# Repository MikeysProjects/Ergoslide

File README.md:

# Ergoslide

## Repo layout

- .github
  - Workflows that build the firmware(s) for the microcontroller that runs the keyboard
- 3d files
  - The source Fusion 360 projects that produce the models for the case
- boards
  - The ZMK shield configuration
- config
  - Global ZMK shield configuration
- images
  - Images (e.g. PNGs, DXFs) needed to create the board or case
- models
  - Output models from Fusion 360 for the case
- pcb
  - The Kicad project for the keyboard PCB
- plates
  - Layouts exported from KLE, useful for creating either 3d models or DXFs for having the top plate manufactured, or automating the layout of the PCB
- zephyr
  - Root Zephyr config

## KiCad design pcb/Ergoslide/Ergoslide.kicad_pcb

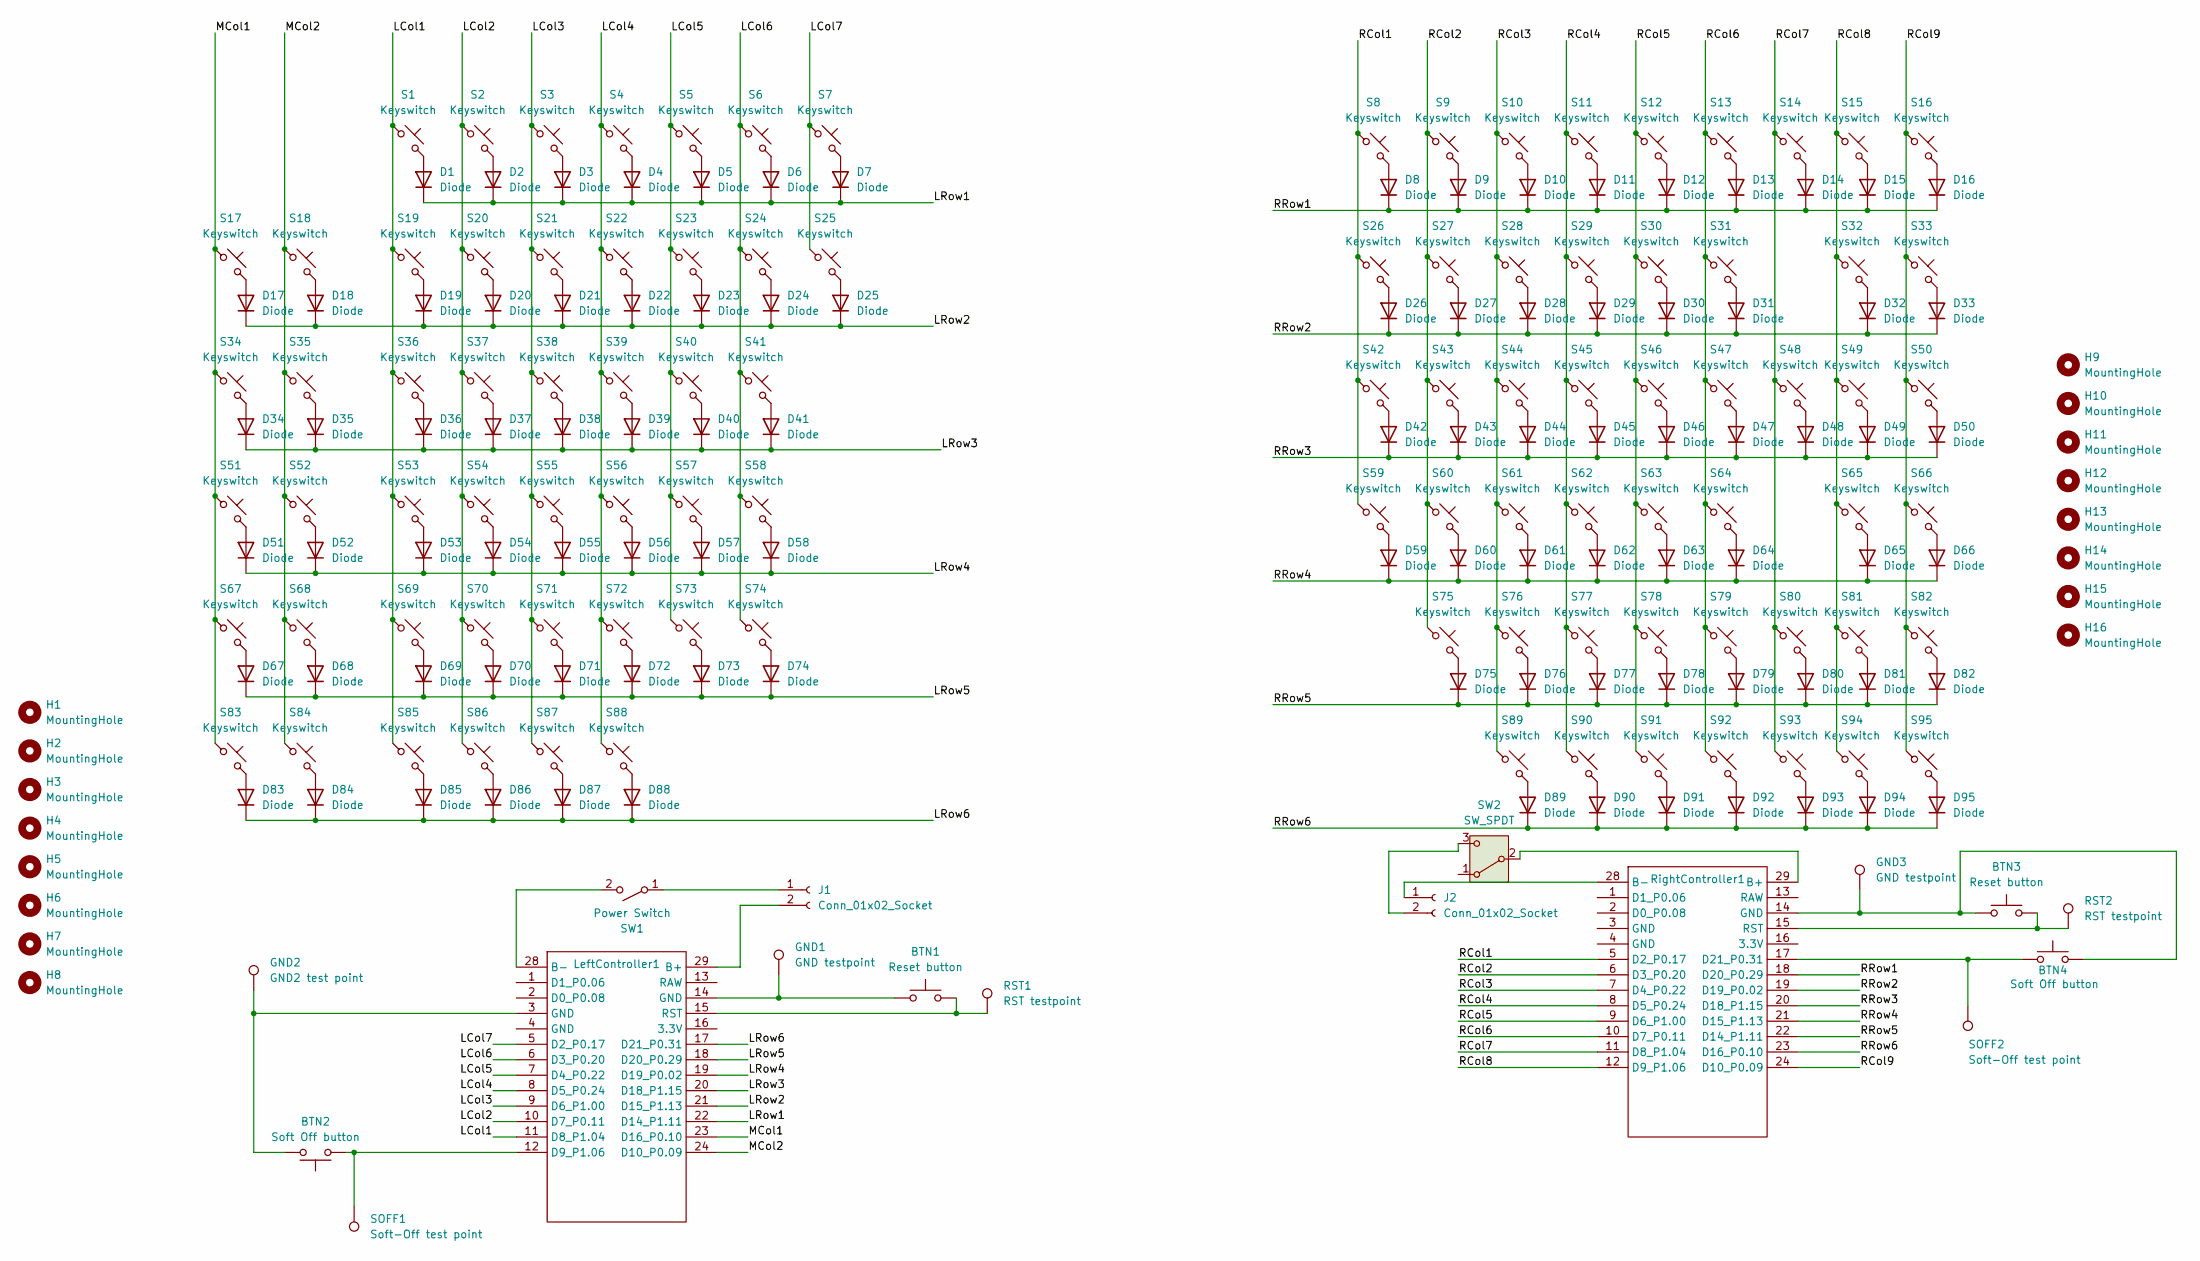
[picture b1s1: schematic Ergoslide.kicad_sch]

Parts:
BTN1, BTN3: Reset button; SW_TL3330AF260QG
BTN2, BTN4: Soft Off button; SW_TL3330AF260QG
D1, D2, D3, D4, D5, D6, D7, D8, D9, D10, D11, D12, D13, D14, D15, D16, D17, D18, D19, D20, D21, D22, D23, D24, D25, D26, D27, D28, D29, D30, D31, D32, D33, D34, D35, D36, D37, D38, D39, D40, D41, D42, D43, D44, D45, D46, D47, D48, D49, D50, D51, D52, D53, D54, D55, D56, D57, D58, D59, D60, D61, D62, D63, D64, D65, D66, D67, D68, D69, D70, D71, D72, D73, D74, D75, D76, D77, D78, D79, D80, D81, D82, D83, D84, D85, D86, D87, D88, D89, D90, D91, D92, D93, D94, D95: Diode; Diode_SOD-123
GND1, GND3: GND testpoint; TestPoint_Pad_2.0x2.0mm
GND2: GND2 test point; TestPoint_Pad_2.0x2.0mm
H1, H2, H3, H4, H5, H6, H7, H8, H9, H10, H11, H12, H13, H14, H15, H16: MountingHole; MountingHole_2.2mm_M2
J1, J2: Conn_01x02_Socket; JST_PH_S2B-PH-K_1x02_P2.00mm_Horizontal
LeftController1: SuperMini NRF52840
RST1, RST2: RST testpoint; TestPoint_Pad_2.0x2.0mm
RightController1: SimpleMini NRF52840
S1, S2, S3, S4, S5, S6, S7, S8, S9, S10, S11, S12, S13, S14, S15, S16, S17, S18, S19, S20, S21, S22, S23, S24, S25, S26, S27, S28, S29, S30, S31, S33, S34, S35, S37, S38, S39, S40, S41, S42, S43, S44, S45, S46, S47, S48, S50, S51, S52, S54, S55, S56, S57, S58, S59, S60, S61, S62, S63, S64, S66, S67, S68, S70, S71, S72, S73, S74, S75, S76, S77, S78, S79, S81, S82, S83, S84, S91, S93, S94, S95: Keyswitch; Gateron-KS33-Hotswap-1U
S32: Keyswitch; Gateron-KS33-Hotswap-2U
S36, S49: Keyswitch; Gateron-KS33-Hotswap-1.5U
S53, S80: Keyswitch; Gateron-KS33-Hotswap-1.75U
S65, S69, S89: Keyswitch; Gateron-KS33-Hotswap-2.25U Stabilized
S85, S86, S87, S90, S92: Keyswitch; Gateron-KS33-Hotswap-1.25U
S88: Keyswitch; Gateron-KS33-Hotswap-2.75U Stabilized
SOFF1, SOFF2: Soft-Off test point; TestPoint_Pad_2.0x2.0mm
SW1: Power Switch; SW_SPDT_CK_JS102011SAQN
SW2: SW_SPDT; SW_SPDT_CK_JS102011SAQN

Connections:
/LCol1: LeftController1.11 (D8_P1.04), S1.1, S19.1, S36.1, S53.1, S69.1, S85.1
/LCol2: LeftController1.10 (D7_P0.11), S2.1, S20.1, S37.1, S54.1, S70.1, S86.1
/LCol3: LeftController1.9 (D6_P1.00), S3.1, S21.1, S38.1, S55.1, S71.1, S87.1
/LCol4: LeftController1.8 (D5_P0.24), S4.1, S22.1, S39.1, S56.1, S72.1, S88.1
/LCol5: LeftController1.7 (D4_P0.22), S5.1, S23.1, S40.1, S57.1, S73.1
/LCol6: LeftController1.6 (D3_P0.20), S6.1, S24.1, S41.1, S58.1, S74.1
/LCol7: LeftController1.5 (D2_P0.17), S7.1, S25.1
/LRow1: D1.1 (K), D2.1 (K), D3.1 (K), D4.1 (K), D5.1 (K), D6.1 (K), D7.1 (K), LeftController1.22 (D14_P1.11)
/LRow2: D17.1 (K), D18.1 (K), D19.1 (K), D20.1 (K), D21.1 (K), D22.1 (K), D23.1 (K), D24.1 (K), D25.1 (K), LeftController1.21 (D15_P1.13)
/LRow3: D34.1 (K), D35.1 (K), D36.1 (K), D37.1 (K), D38.1 (K), D39.1 (K), D40.1 (K), D41.1 (K), LeftController1.20 (D18_P1.15)
/LRow4: D51.1 (K), D52.1 (K), D53.1 (K), D54.1 (K), D55.1 (K), D56.1 (K), D57.1 (K), D58.1 (K), LeftController1.19 (D19_P0.02)
/LRow5: D67.1 (K), D68.1 (K), D69.1 (K), D70.1 (K), D71.1 (K), D72.1 (K), D73.1 (K), D74.1 (K), LeftController1.18 (D20_P0.29)
/LRow6: D83.1 (K), D84.1 (K), D85.1 (K), D86.1 (K), D87.1 (K), D88.1 (K), LeftController1.17 (D21_P0.31)
/MCol1: LeftController1.23 (D16_P0.10), S17.1, S34.1, S51.1, S67.1, S83.1
/MCol2: LeftController1.24 (D10_P0.09), S18.1, S35.1, S52.1, S68.1, S84.1
/RCol1: RightController1.5 (D2_P0.17), S8.1, S26.1, S42.1, S59.1
/RCol2: RightController1.6 (D3_P0.20), S9.1, S27.1, S43.1, S60.1, S75.1
/RCol3: RightController1.7 (D4_P0.22), S10.1, S28.1, S44.1, S61.1, S76.1, S89.1
/RCol4: RightController1.8 (D5_P0.24), S11.1, S29.1, S45.1, S62.1, S77.1, S90.1
/RCol5: RightController1.9 (D6_P1.00), S12.1, S30.1, S46.1, S63.1, S78.1, S91.1
/RCol6: RightController1.10 (D7_P0.11), S13.1, S31.1, S47.1, S64.1, S79.1, S92.1
/RCol7: RightController1.11 (D8_P1.04), S14.1, S48.1, S80.1, S93.1
/RCol8: RightController1.12 (D9_P1.06), S15.1, S32.1, S49.1, S65.1, S81.1, S94.1
/RCol9: RightController1.24 (D10_P0.09), S16.1, S33.1, S50.1, S66.1, S82.1, S95.1
/RRow1: D8.1 (K), D9.1 (K), D10.1 (K), D11.1 (K), D12.1 (K), D13.1 (K), D14.1 (K), D15.1 (K), D16.1 (K), RightController1.18 (D20_P0.29)
/RRow2: D26.1 (K), D27.1 (K), D28.1 (K), D29.1 (K), D30.1 (K), D31.1 (K), D32.1 (K), D33.1 (K), RightController1.19 (D19_P0.02)
/RRow3: D42.1 (K), D43.1 (K), D44.1 (K), D45.1 (K), D46.1 (K), D47.1 (K), D48.1 (K), D49.1 (K), D50.1 (K), RightController1.20 (D18_P1.15)
/RRow4: D59.1 (K), D60.1 (K), D61.1 (K), D62.1 (K), D63.1 (K), D64.1 (K), D65.1 (K), D66.1 (K), RightController1.21 (D15_P1.13)
/RRow5: D75.1 (K), D76.1 (K), D77.1 (K), D78.1 (K), D79.1 (K), D80.1 (K), D81.1 (K), D82.1 (K), RightController1.22 (D14_P1.11)
/RRow6: D89.1 (K), D90.1 (K), D91.1 (K), D92.1 (K), D93.1 (K), D94.1 (K), D95.1 (K), RightController1.23 (D16_P0.10)
unnamed: BTN2.2, GND2.1, LeftController1.3 (GND)
unnamed: BTN3.1, BTN4.2, GND3.1, RightController1.14 (GND)
unnamed: D1.2 (A), S1.2
unnamed: D2.2 (A), S2.2
unnamed: D3.2 (A), S3.2
unnamed: D4.2 (A), S4.2
unnamed: D5.2 (A), S5.2
unnamed: D6.2 (A), S6.2
unnamed: D7.2 (A), S7.2
unnamed: D8.2 (A), S8.2
unnamed: D9.2 (A), S9.2
unnamed: D10.2 (A), S10.2
unnamed: D11.2 (A), S11.2
unnamed: D12.2 (A), S12.2
unnamed: D13.2 (A), S13.2
unnamed: D14.2 (A), S14.2
unnamed: D15.2 (A), S15.2
unnamed: D16.2 (A), S16.2
unnamed: D17.2 (A), S17.2
unnamed: D18.2 (A), S18.2
unnamed: D19.2 (A), S19.2
unnamed: D20.2 (A), S20.2
unnamed: D21.2 (A), S21.2
unnamed: D22.2 (A), S22.2
unnamed: D23.2 (A), S23.2
unnamed: D24.2 (A), S24.2
unnamed: D25.2 (A), S25.2
unnamed: D26.2 (A), S26.2
unnamed: D27.2 (A), S27.2
unnamed: D28.2 (A), S28.2
unnamed: D29.2 (A), S29.2
unnamed: D30.2 (A), S30.2
unnamed: D31.2 (A), S31.2
unnamed: D32.2 (A), S32.2
unnamed: D33.2 (A), S33.2
unnamed: D34.2 (A), S34.2
unnamed: D35.2 (A), S35.2
unnamed: D36.2 (A), S36.2
unnamed: D37.2 (A), S37.2
unnamed: D38.2 (A), S38.2
unnamed: D39.2 (A), S39.2
unnamed: D40.2 (A), S40.2
unnamed: D41.2 (A), S41.2
unnamed: D42.2 (A), S42.2
unnamed: D43.2 (A), S43.2
unnamed: D44.2 (A), S44.2
unnamed: D45.2 (A), S45.2
unnamed: D46.2 (A), S46.2
unnamed: D47.2 (A), S47.2
unnamed: D48.2 (A), S48.2
unnamed: D49.2 (A), S49.2
unnamed: D50.2 (A), S50.2
unnamed: D51.2 (A), S51.2
unnamed: D52.2 (A), S52.2
unnamed: D53.2 (A), S53.2
unnamed: D54.2 (A), S54.2
unnamed: D55.2 (A), S55.2
unnamed: D56.2 (A), S56.2
unnamed: D57.2 (A), S57.2
unnamed: D58.2 (A), S58.2
unnamed: D59.2 (A), S59.2
unnamed: D60.2 (A), S60.2
unnamed: D61.2 (A), S61.2
unnamed: D62.2 (A), S62.2
unnamed: D63.2 (A), S63.2
unnamed: D64.2 (A), S64.2
unnamed: D65.2 (A), S65.2
unnamed: D66.2 (A), S66.2
unnamed: D67.2 (A), S67.2
unnamed: D68.2 (A), S68.2
unnamed: D69.2 (A), S69.2
unnamed: D70.2 (A), S70.2
unnamed: D71.2 (A), S71.2
unnamed: D72.2 (A), S72.2
unnamed: D73.2 (A), S73.2
unnamed: D74.2 (A), S74.2
unnamed: D75.2 (A), S75.2
unnamed: D76.2 (A), S76.2
unnamed: D77.2 (A), S77.2
unnamed: D78.2 (A), S78.2
unnamed: D79.2 (A), S79.2
unnamed: D80.2 (A), S80.2
unnamed: D81.2 (A), S81.2
unnamed: D82.2 (A), S82.2
unnamed: D83.2 (A), S83.2
unnamed: D84.2 (A), S84.2
unnamed: D85.2 (A), S85.2
unnamed: D86.2 (A), S86.2
unnamed: D87.2 (A), S87.2
unnamed: D88.2 (A), S88.2
unnamed: D89.2 (A), S89.2
unnamed: D90.2 (A), S90.2
unnamed: D91.2 (A), S91.2
unnamed: D92.2 (A), S92.2
unnamed: D93.2 (A), S93.2
unnamed: D94.2 (A), S94.2
unnamed: D95.2 (A), S95.2
unnamed 128: BTN1.1, GND1.1, LeftController1.14 (GND); also elsewhere on the board
unnamed: J1.1, SW1.1 (A)
unnamed: J1.2, LeftController1.29 (B+)
unnamed: J2.1, RightController1.28 (B-)
unnamed: J2.2, SW2.3 (C)
unnamed: LeftController1.28 (B-), SW1.2 (B)
unnamed 134: LeftController1.1 (D1_P0.06); also elsewhere on the board
unnamed: BTN2.1, LeftController1.12 (D9_P1.06), SOFF1.1
unnamed: BTN1.2, LeftController1.15 (RST), RST1.1
unnamed: RightController1.29 (B+), SW2.2 (B)
unnamed: BTN4.1, RightController1.17 (D21_P0.31), SOFF2.1
unnamed: BTN3.2, RST2.1, RightController1.15 (RST)

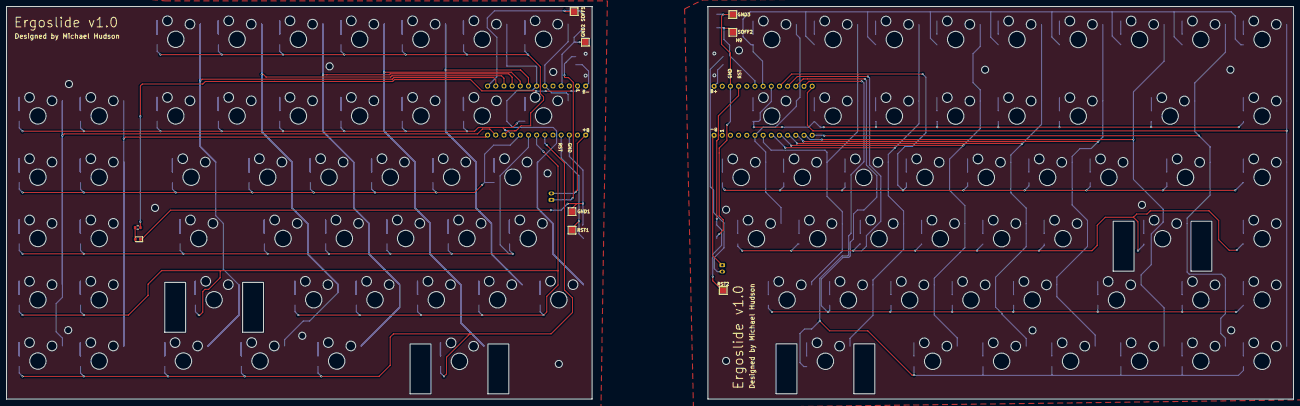
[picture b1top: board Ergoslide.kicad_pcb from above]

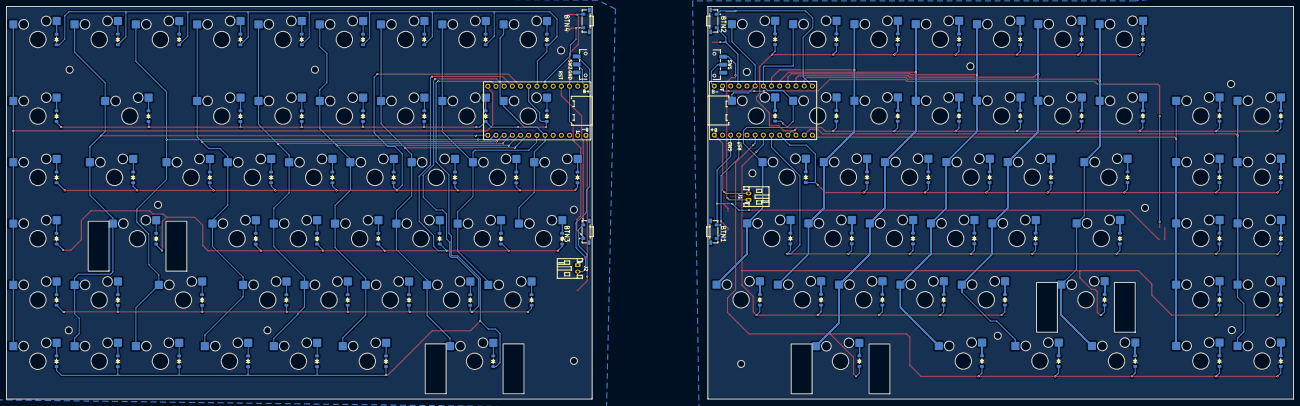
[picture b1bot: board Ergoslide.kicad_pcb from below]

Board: 2 copper layers, 400.0 x 122.0 mm, 225 parts (200 on the bottom side), 140 nets.

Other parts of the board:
D96: LED; LED_0603_1608Metric
R1: Resistor; R_0603_1608Metric

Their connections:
unnamed: D96.2 (A), R1.2
unnamed 128: D96.1 (K); also elsewhere on the board
unnamed 134: R1.1; also elsewhere on the board

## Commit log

2025-03-16 Set up the Ergoslide for testing
2025-03-16 Fix bad flag name for row-gpios
2025-03-16 Another semicolon, why not?
2025-03-16 Fix compatibility name
2025-03-16 Correct column count
2025-03-16 Hopefully there's a sale on semicolons
2025-03-16 Buy one semicolon, get one free
2025-03-16 Add bluetooth
2025-03-16 Add BT_CLR_ALL key
2025-03-16 Add BT_CLR command
2025-03-16 Better BT keymap config
2025-03-16 Try something more obvious to differentiate firmware
2025-03-16 Hail mary
2025-03-16 Remove BT
2025-03-16 Update keymap in config directory too
2025-03-16 Add settings_reset build
2025-03-16 Add plate layout
2025-07-30 Update the layout of the Ergoslide to have macro keys on the left hand side
2025-07-31 Update the spacing on the left and right sides of the board
    This will make the left and right halves exactly the same
    width in terms of the keys used
2025-07-31 Fix bad rename for plates
2025-07-31 Start wiring up the PCB
2025-08-01 Fully route the matrix
2025-08-01 Muck about with custom footprints and symbols for the Supermini
    Started wiring the Supermini in to the left side matrix
2025-08-11 Set up the board for PCB testing
2025-08-11 Move a printable key to the top-left slot
2025-08-11 Try some shenanigans to figure out why the wrong macro column is being triggered
2025-08-11 Add row definitions to the right half of the board
2025-08-11 Switch some pins around
2025-08-11 Clean up pcb directory in Git
2025-08-12 Fill out the keymap for the left half
2025-08-12 Update right hand offset
2025-08-12 Update keymap transform to match row and column layout
2025-08-12 Switch the top two rows around
2025-08-12 Remove text from testing the new keymap
    Whoops
2025-08-12 Set up physical key layout
2025-08-12 Import the physical layout in to the main dtsi
2025-08-12 Add studio to the features metadata
2025-08-12 Change import style
2025-08-12 Add the USB UART and ZMK Studio flag to the build config
2025-08-12 Set the physical layout using the same name as in the docs
2025-08-12 Use the same name in more places
2025-08-12 Try again
2025-08-12 Use the physical layout for the node name (I think, I don't really understand this config language)
2025-08-12 Move the layout node outside of whatever the forward-slash declaration is
    It looks like this in the Corne dtis so... good luck I guess
2025-08-12 Add ZMK Studio unlock button
2025-08-24 Set up the Ergoslide for testing
    Author: MikeysProjects <michael.andrew.hudson@gmail.com>
2025-11-17 Add the bottom pattern image for the case, as well as the Fusion project and exported STEP file
2025-11-17 Attempt to get soft off behavior working
2025-11-17 Remove redundant node
2025-11-17 Shorten time needed to activate soft-off, and don't wake up on keypress
2025-11-17 Move the sleep config to another file in an attempt to get soft-sleep working
2025-11-17 Add external power and don't allow anything to wake up the board
2025-11-17 Remove external_power node
2025-11-17 Re-enable wakeup sources
2025-11-18 Ignore some more temp files from Kicad
2025-11-18 Add some more interesting default keys to the keymap
2026-01-28 Add TL3330AF260GQ to the PCB, start wiring up the second half
2026-02-19 Finish wiring up right hand side PCB
2026-02-19 Add fill zones
2026-03-07 Use stabilized switch cutouts
2026-03-07 Update ZMK build target for board revisions
2026-03-07 Use ZMK board variant in build matrix
2026-03-07 Add Caps Lock indicator LED support
2026-03-07 Flip some rows
2026-03-07 Unflip rows
2026-03-07 Disable UART0 to free D1 for Caps Lock LED
2026-03-07 Move nice!nano UART override to board overlay
2026-03-07 Use P1.01 for Caps Lock LED testing
2026-03-07 Use onboard LED for Caps Lock testing
2026-03-07 Force D1 Caps Lock LED on at boot
2026-03-07 Add compile check for caps lock LED source
2026-03-07 Move HID indicator config into shield defconfig
2026-03-07 Add ZMK app include path for module sources
2026-03-07 Build Caps Lock LED source into ZMK app target
2026-03-07 Enable GPIO LED driver for Caps Lock LED
2026-03-08 Add Caps Lock LED, remove labels for holes, realign labels for everything else
2026-03-08 Add some tacky text saying who made this thing
2026-03-19 Update keymap to match updated row/col connections to the mcu
2026-03-19 Some small update to the PCB
2026-03-21 Add the right hand side to the keymap and layout
2026-03-21 Clean up mistyped keycodes
2026-03-21 Whoops, missed PAUSE not being valid
2026-03-21 Increase column offset for right hand side
    I think I must have never bumped this after I added the macro columns
2026-03-21 Align the Row/Column coordinates used with the actual matrix
2026-03-21 Restructure the keymap to match the matrix in Kicad
